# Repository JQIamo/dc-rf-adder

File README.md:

# DC/RF Adder circuit

Simple op-amp adder (4 channels), to add a DC offset to an RF signal.

Used, for example, in the Sr lab to do parametric heating in our dipole trap. A small RF dither is added onto the DC setpoint sent to the dipole intensity lock.

## 2CH Edgemount POT

This circuit is a two-channel version, where the DC value is summed in via potentiometer.

## Characterization

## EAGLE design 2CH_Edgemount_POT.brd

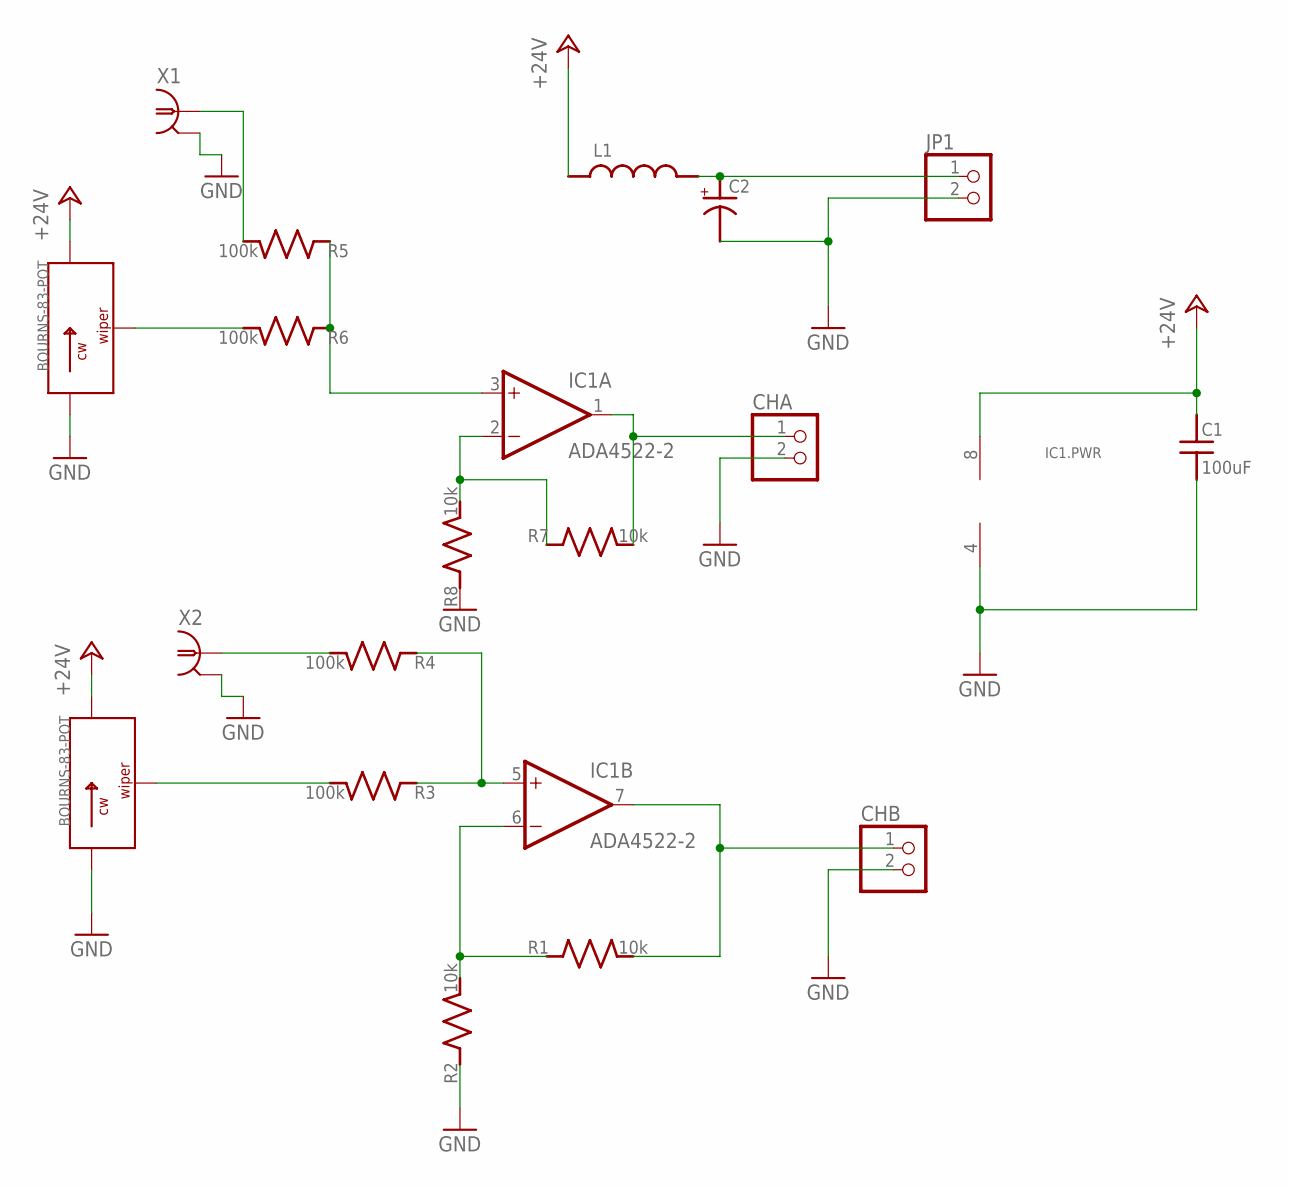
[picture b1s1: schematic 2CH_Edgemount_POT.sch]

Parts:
C1: 100uF; C_MLCC_0603
C2: C_POL_SMDF; PANASONIC_F
CHA: PINHD-1X2; 1X02
CHB: PINHD-1X2; 1X02
IC1: ADA4522-2; SO08
JP1: PINHD-1X2; 1X02
L1: L_FERRITE_SMDLFERRITE_0805; R_0805
R1, R2, R7, R8: 10k; R_1206
R3, R4, R5, R6: 100k; R_1206
R9, R10: BOURNS-83-POT; BOURNS83
X1, X2: BNC-H; BNC90

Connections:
+24V: C1.P$1 (1), IC1.8 (V+), L1.P$1 (1), R9.P$3, R10.P$3
CHB: CHB.1, IC1.7 (OUT), R1.P$2 (2)
GND: C1.P$2 (2), C2.-, CHA.2, CHB.2, IC1.4 (V-), JP1.2, R2.P$1 (1), R8.P$1 (1), R9.P$1, R10.P$1, X1.2, X2.2
unnamed: R6.P$2 (2), R9.P$2
unnamed: R3.P$2 (2), R10.P$2
unnamed: IC1.6 (-IN), R1.P$1 (1), R2.P$2 (2)
unnamed: IC1.5 (+IN), R3.P$1 (1), R4.P$1 (1)
unnamed: IC1.2 (-IN), R7.P$1 (1), R8.P$2 (2)
unnamed: CHA.1, IC1.1 (OUT), R7.P$2 (2)
unnamed: IC1.3 (+IN), R5.P$1 (1), R6.P$1 (1)
unnamed: R4.P$2 (2), X2.1
unnamed: R5.P$2 (2), X1.1
unnamed: C2.+, JP1.1, L1.P$2 (2)

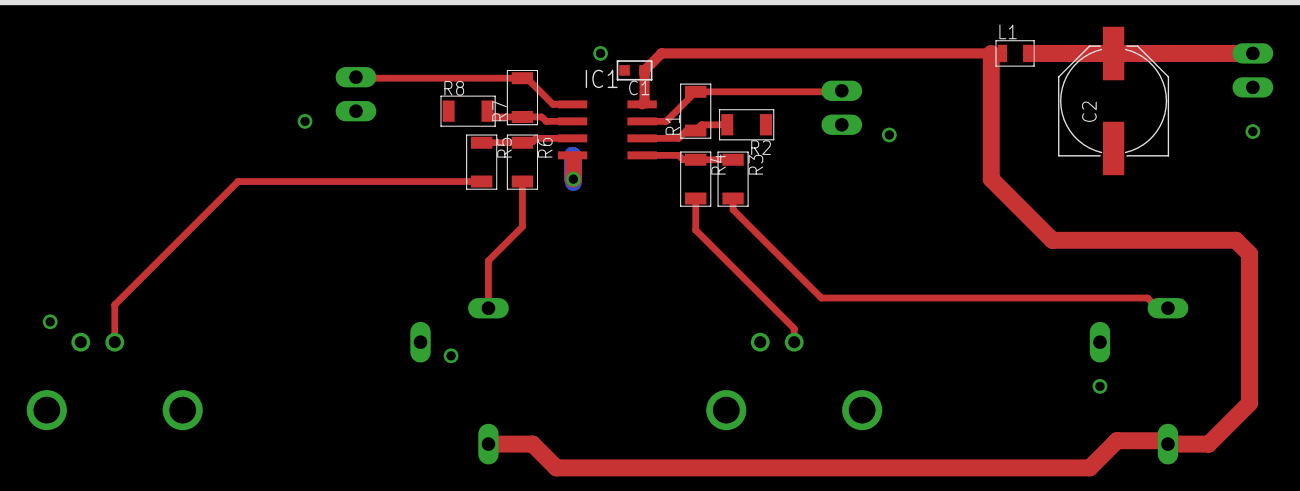
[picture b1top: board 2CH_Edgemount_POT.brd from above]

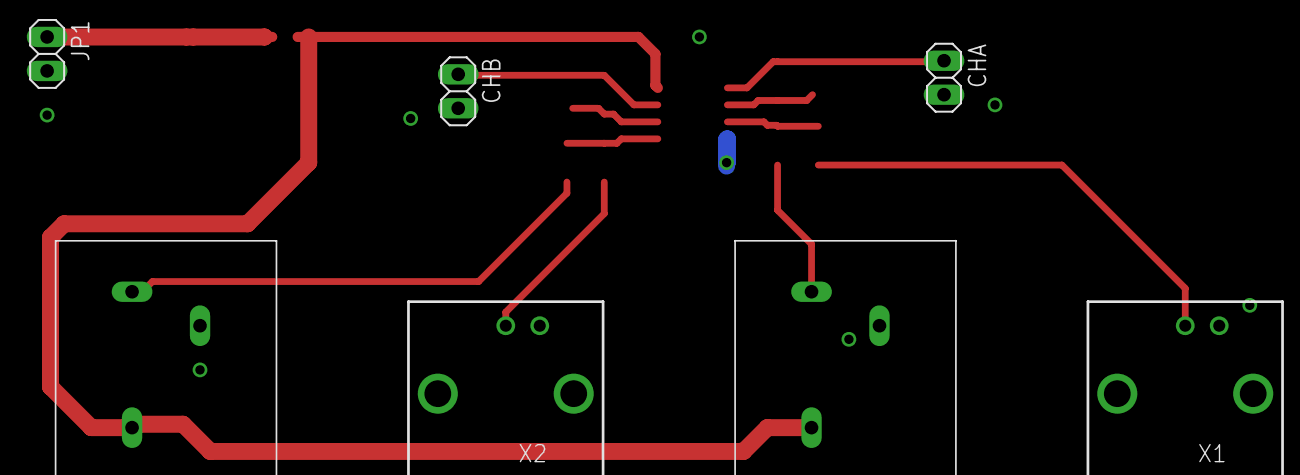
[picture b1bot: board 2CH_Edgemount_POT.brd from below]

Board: 2 copper layers, 19 parts (7 on the bottom side), 13 nets.

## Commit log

2014-10-31 Single channel DC Adder circuit.
    Mid-development, mostly committing to initialize the repository and
    push to GitHub.
2015-01-01 Added .gitignore, README, and measured transfer functions
2015-01-01 Added transfer function plots to README file
2015-01-01 Fixed name of RF Transfer Function image
2016-01-30 Added 2CH_Edgemount_POT -- sum DC voltage with pot
    DC setpoint using potentiometer; sum in RF via BNC.
